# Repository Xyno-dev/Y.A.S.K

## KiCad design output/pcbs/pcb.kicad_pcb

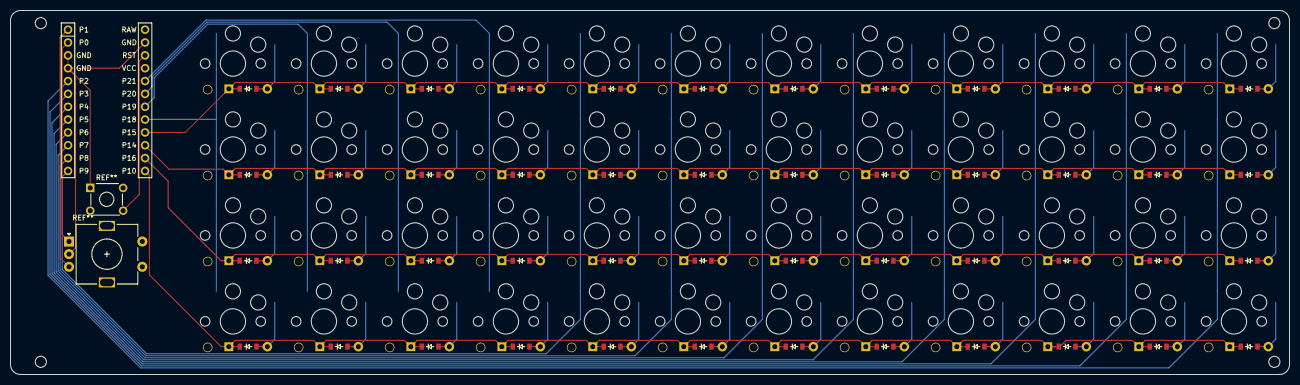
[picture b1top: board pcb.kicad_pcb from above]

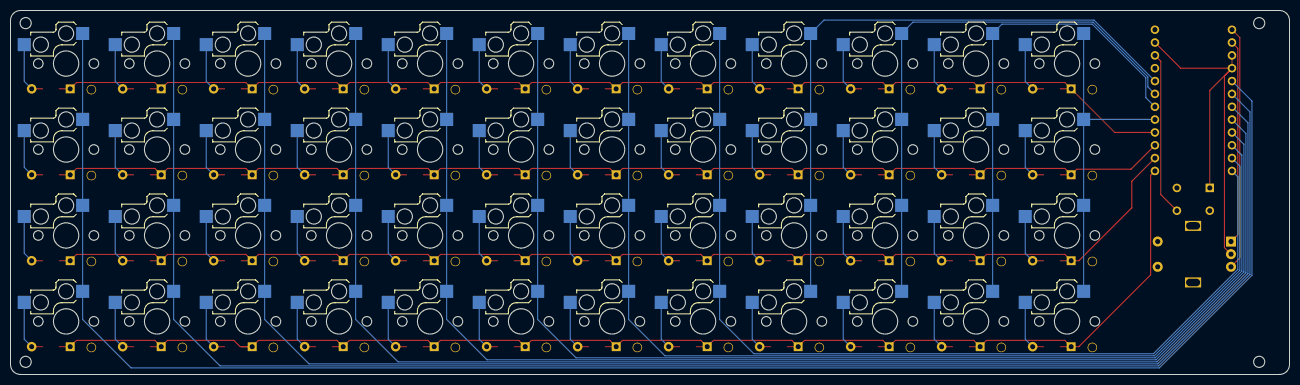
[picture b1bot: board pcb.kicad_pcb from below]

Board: 2 copper layers, 253.0 x 72.0 mm, 101 parts (48 on the bottom side), 65 nets.

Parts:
D1, D2, D3, D4, D5, D6, D7, D8, D9, D10, D11, D12, D13, D14, D15, D16, D17, D18, D19, D20, D21, D22, D23, D24, D25, D26, D27, D28, D29, D30, D31, D32, D33, D34, D35, D36, D37, D38, D39, D40, D41, D42, D43, D44, D45, D46, D47, D48: diode_tht_sod123
MCU1: mcu_supermini_nrf52840
MH1, MH2, MH3, MH4: mounting_hole_npth
S1, S2, S3, S4, S5, S6, S7, S8, S9, S10, S11, S12, S13, S14, S15, S16, S17, S18, S19, S20, S21, S22, S23, S24, S25, S26, S27, S28, S29, S30, S31, S32, S33, S34, S35, S36, S37, S38, S39, S40, S41, S42, S43, S44, S45, S46, S47, S48: switch_choc_v1_v2

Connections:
GND: MCU1.2, MCU1.21, MCU1.22
P2: MCU1.20, S45.1, S46.1, S47.1, S48.1
P3: MCU1.19, S41.1, S42.1, S43.1, S44.1
P4: MCU1.18, S37.1, S38.1, S39.1, S40.1
P5: MCU1.17, S33.1, S34.1, S35.1, S36.1
P6: MCU1.16, S29.1, S30.1, S31.1, S32.1
P7: MCU1.15, S25.1, S26.1, S27.1, S28.1
P8: MCU1.14, S21.1, S22.1, S23.1, S24.1
P9: MCU1.13, S17.1, S18.1, S19.1, S20.1
P10: D1.1, D5.1, D9.1, D13.1, D17.1, D21.1, D25.1, D29.1, D33.1, D37.1, D41.1, D45.1, MCU1.12
P14: D3.1, D7.1, D11.1, D15.1, D19.1, D23.1, D27.1, D31.1, D35.1, D39.1, D43.1, D47.1, MCU1.10
P15: D4.1, D8.1, D12.1, D16.1, D20.1, D24.1, D28.1, D32.1, D36.1, D40.1, D44.1, D48.1, MCU1.9
P16: D2.1, D6.1, D10.1, D14.1, D18.1, D22.1, D26.1, D30.1, D34.1, D38.1, D42.1, D46.1, MCU1.11
P18: MCU1.8, S1.1, S2.1, S3.1, S4.1
P19: MCU1.7, S5.1, S6.1, S7.1, S8.1
P20: MCU1.6, S9.1, S10.1, S11.1, S12.1
P21: MCU1.5, S13.1, S14.1, S15.1, S16.1
eight_bottom: D30.2, S30.2
eight_home: D31.2, S31.2
eight_mod: D29.2, S29.2
eight_top: D32.2, S32.2
eleven_bottom: D42.2, S42.2
eleven_home: D43.2, S43.2
eleven_mod: D41.2, S41.2
eleven_top: D44.2, S44.2
five_bottom: D18.2, S18.2
five_home: D19.2, S19.2
five_mod: D17.2, S17.2
five_top: D20.2, S20.2
four_bottom: D14.2, S14.2
four_home: D15.2, S15.2
four_mod: D13.2, S13.2
four_top: D16.2, S16.2
nine_bottom: D34.2, S34.2
nine_home: D35.2, S35.2
nine_mod: D33.2, S33.2
nine_top: D36.2, S36.2
one_bottom: D2.2, S2.2
one_home: D3.2, S3.2
one_mod: D1.2, S1.2
one_top: D4.2, S4.2
seven_bottom: D26.2, S26.2
seven_home: D27.2, S27.2
seven_mod: D25.2, S25.2
seven_top: D28.2, S28.2
six_bottom: D22.2, S22.2
six_home: D23.2, S23.2
six_mod: D21.2, S21.2
six_top: D24.2, S24.2
ten_bottom: D38.2, S38.2
ten_home: D39.2, S39.2
ten_mod: D37.2, S37.2
ten_top: D40.2, S40.2
three_bottom: D10.2, S10.2
three_home: D11.2, S11.2
three_mod: D9.2, S9.2
three_top: D12.2, S12.2
twelve_bottom: D46.2, S46.2
twelve_home: D47.2, S47.2
twelve_mod: D45.2, S45.2
twelve_top: D48.2, S48.2
two_bottom: D6.2, S6.2
two_home: D7.2, S7.2
two_mod: D5.2, S5.2
two_top: D8.2, S8.2

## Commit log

2025-06-06 chore: initial commit
    Cleaned up version of the first Y.A.S.K which was built using the web
    version of ergogen.
2025-06-06 chore: remove lock file
2025-06-06 chore: ran drc
